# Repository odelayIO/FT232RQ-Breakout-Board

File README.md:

##### View on [gh-page](https://odelayio.github.io/FT232RQ-Breakout-Board/)

# FTDI FT232RQ Breakout Board with Variable LDO for VIO

## Board Features:

- Capability to configure microcontrollers directly (e.g. CC430F5137) 
-	Configurable VCCIO between 1.8V to 5V using on-board LDO
-	Data Rate Max 3,000,000 BAUD (FTDI FT232R Chip)
-	Route the RTS and DTR to a header for easy mode as a Programmer
- TX and RX LED (Red/Green)
-	Small form factor

<br>
<br>

<br>
<br>
   
## Reflowing QFN-32 FTDI FT232RQ Chip:

First attempt to reflow a QFN-32 device to a board without purchasing expensive equipment.  I used a hot air gun that I purchased on Amazon for $14 ( TruePower 01-0712 Mini Heat Gun, Blue).  I also used solder paste that melts at 183C degrees.  

###Applied the solder paste:

<br>

###Placed QFN-32 Device

<br>

###Final Product being used to configure a CC430F5137 microcontroller

<br>
<br>

## Documents:

- Eagle_SCH_BRD_GERBER
  * Schematic, Layout and Gerber files
- FTDI_EEPROM_Configuration.xml
  * Configuration file used to configure the FT232RQ device
- Verify_Serial_Communications.py 
  * Simple Python script to test the serial communications between a reference USB design and the Unit Under Test (UUT)

<br>
<br>

## Parts List

| Part               | Part Number        | Unit Price | Notes         | Link                                                                                                                         |
|--------------------|--------------------|------------|---------------|------------------------------------------------------------------------------------------------------------------------------|
| USB Mini Connector | 151-1206-1-ND      | $6.55      | 10 Connectors | http://www.digikey.com/product-detail/en/edac-inc/690-005-299-043/151-1206-1-ND/4312192                                      |
| FTDI FT232RQ       | 768-1008-1-ND      | $4.50      | 1             | http://www.digikey.com/product-detail/en/ftdi-future-technology-devices-international-ltd/FT232RQ-REEL/768-1008-1-ND/1836403 |
| LM317              | 768-1008-1-ND      | $0.77      | In stock      | http://www.digikey.com/product-detail/en/texas-instruments/LM317DCYR/296-12602-1-ND/443738                                   |
| 0.1uF, 0402, Cap   | 490-6328-1-ND      | $0.55      | 100 capacitor | http://www.digikey.com/product-detail/en/murata-electronics-north-america/GRM155R71C104KA88J/490-6328-1-ND/3845525           |
| 10uF, 0805, Cap    | 1276-6456-1-ND     | $0.78      | 10 capacitor  | http://www.digikey.com/product-detail/en/samsung-electro-mechanics-america-inc/CL21A106KPFNNNG/1276-6456-1-ND/5958084        |
| 143 ohm, 0402      | YAG2980CT-ND       | $0.48      | 100 resistors | http://www.digikey.com/product-detail/en/yageo/RC0402FR-07143RL/YAG2980CT-ND/5281845                                         |
| 240 ohm, 0402      | 311-240JRCT-ND     | $0.47      | 100 resistors | http://www.digikey.com/product-detail/en/yageo/RC0402JR-07240RL/311-240JRCT-ND/729393                                        |
| 392 ohm, 0402      | YAG3145CT-ND       | $0.48      | 100 resistors | http://www.digikey.com/product-detail/en/yageo/RC0402FR-07392RL/YAG3145CT-ND/5282010                                         |
| 1k ohm, 0402       | 311-1.0KJRCT-ND    | $0.47      | 100 resistors | http://www.digikey.com/product-detail/en/yageo/RC0402JR-071KL/311-1.0KJRCT-ND/729355                                         |
| Red LED            | SML-D12V1WT86CT-ND | $1.71      | 10 LEDs       | http://www.digikey.com/product-detail/en/rohm-semiconductor/SML-D12V1WT86/SML-D12V1WT86CT-ND/5843857                         |
| Yellow/Green LED   | SML-D12M1WT86CT-ND | $1.71      | 10 LEDs       | http://www.digikey.com/product-detail/en/rohm-semiconductor/SML-D12M1WT86/SML-D12M1WT86CT-ND/5843861                         |
| PCB Fab            | 2 layer prototype  | $5.00      | 3 copies      | http://docs.oshpark.com/services/two-layer/                                                                                  |
|                    |                    |            |               |                                                                                                                              |

<br>
<br>

## Additional Information:
- Fab board at [https://oshpark.com/](https://oshpark.com/)
  - Gerber Zip Package was used to fab board

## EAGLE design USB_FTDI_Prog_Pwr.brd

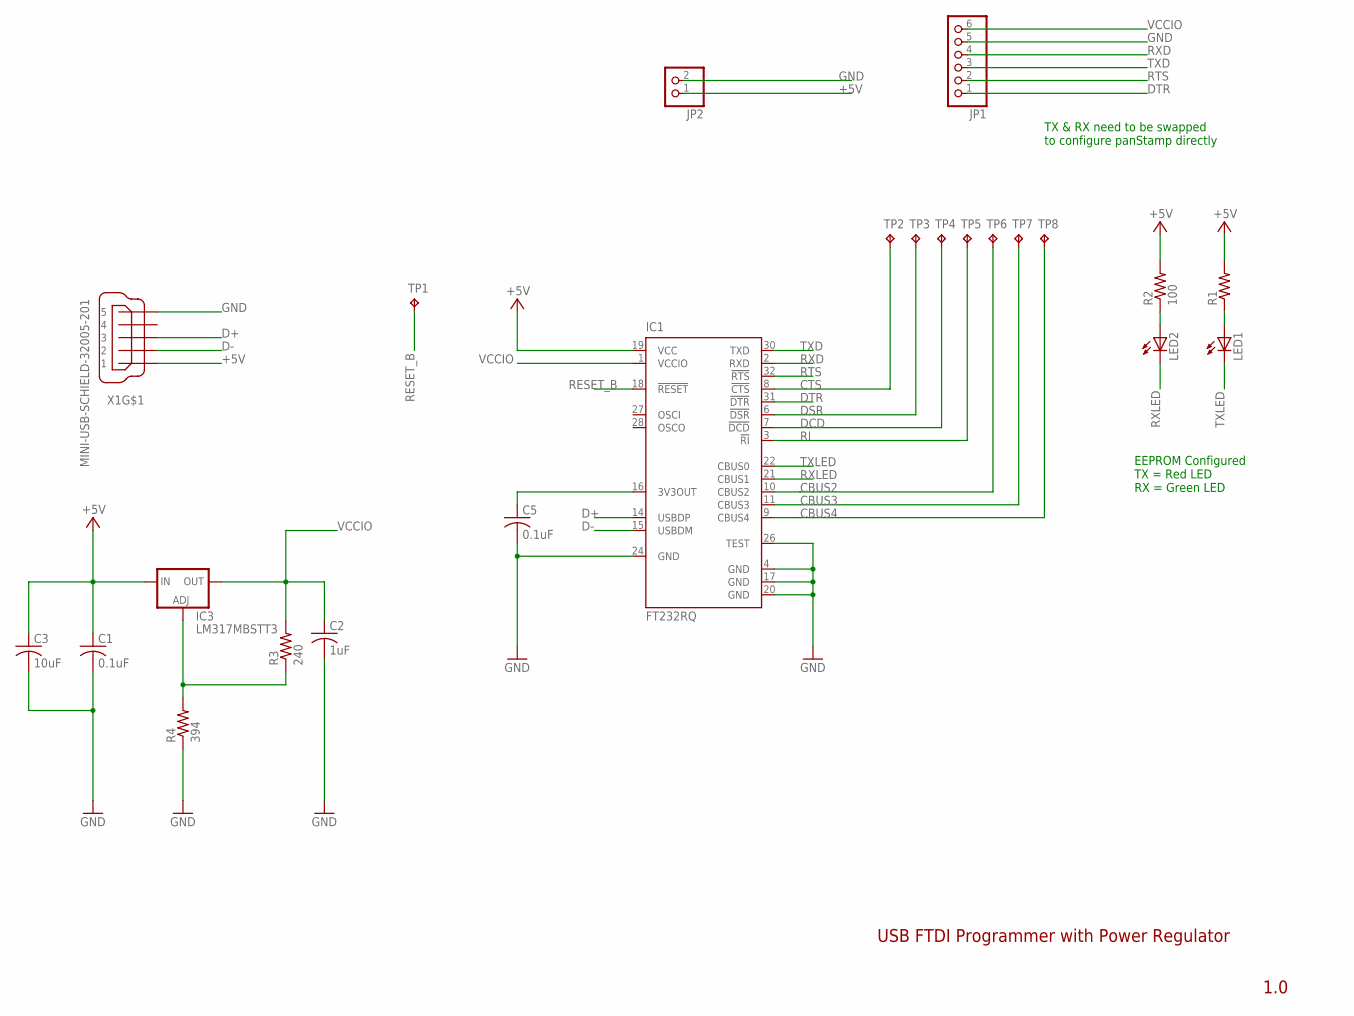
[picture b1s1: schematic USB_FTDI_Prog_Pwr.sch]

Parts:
C1, C5: 0.1uF; C0402
C2: 1uF; C0402
C3: 10uF; C0603
IC1: FT232RQ; QFN32
IC3: LM317MBSTT3; SOT223
JP1: PINHD-1X6; 1X06
JP2: PINHD-1X2; 1X02
LED1, LED2: LEDCHIP-LED0603; CHIP-LED0603
R1: R-US_R0402; R0402
R2: 100; R0402
R3: 240; R0402
R4: 394; R0402
TP1, TP2, TP3, TP4, TP5, TP6, TP7, TP8: TPB1,27; B1,27
X1: MINI-USB-SCHIELD-32005-201; 32005-201

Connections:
+5V: C1.1, C3.1, IC1.19 (VCC), IC3.3 (IN), JP2.1, R1.2, R2.2, X1.1
CBUS2: IC1.10 (CBUS2), TP6.TP
CBUS3: IC1.11 (CBUS3), TP7.TP
CBUS4: IC1.9 (CBUS4), TP8.TP
CTS: IC1.8 (!CTS), TP2.TP
D+: IC1.14 (USBDP), X1.3
D-: IC1.15 (USBDM), X1.2
DCD: IC1.7 (!DCD), TP4.TP
DSR: IC1.6 (!DSR), TP3.TP
DTR: IC1.31 (!DTR), JP1.1
GND: C1.2, C2.2, C3.2, C5.2, IC1.4 (GND), IC1.17 (GND), IC1.20 (GND), IC1.24 (GND), IC1.26 (TEST), JP1.5, JP2.2, R4.1, X1.5
unnamed: LED1.A, R1.1
unnamed: IC3.1 (ADJ), R3.1, R4.2
unnamed: C5.1, IC1.16 (3V3OUT)
unnamed: LED2.A, R2.1
RESET_B: IC1.18 (!RESET), TP1.TP
RI: IC1.3 (!RI), TP5.TP
RTS: IC1.32 (!RTS), JP1.2
RXD: IC1.2 (RXD), JP1.4
RXLED: IC1.21 (CBUS1), LED2.C
TXD: IC1.30 (TXD), JP1.3
TXLED: IC1.22 (CBUS0), LED1.C
VCCIO: C2.1, IC1.1 (VCCIO), IC3.4 (OUT), JP1.6, R3.2

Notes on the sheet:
USB FTDI Programmer with Power Regulator
1.0
EEPROM Configured TX = Red LED RX = Green LED
TX & RX need to be swapped to configure panStamp directly

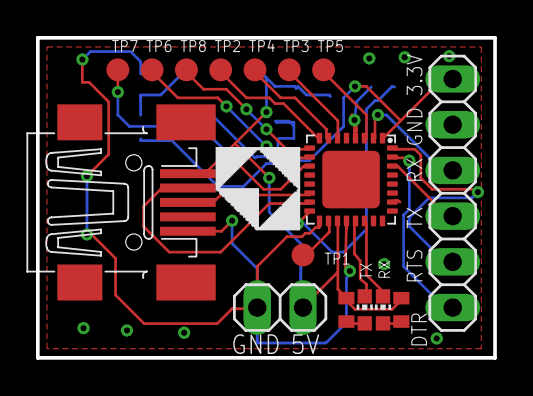
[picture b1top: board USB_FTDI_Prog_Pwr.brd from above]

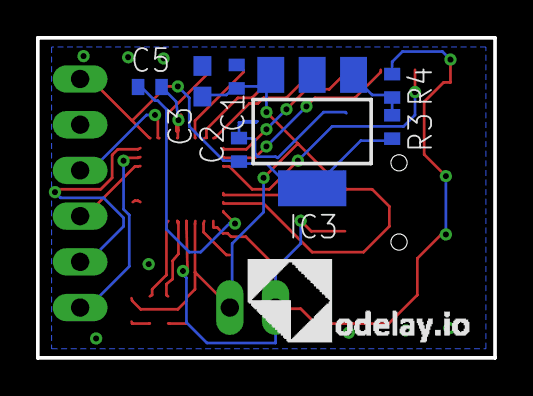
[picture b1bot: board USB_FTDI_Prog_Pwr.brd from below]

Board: 2 copper layers, 25.4 x 17.8 mm, 23 parts (7 on the bottom side), 23 nets.

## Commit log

2016-09-22 Create gh-pages branch via GitHub
2016-09-22 adding source code and Eagle board files
